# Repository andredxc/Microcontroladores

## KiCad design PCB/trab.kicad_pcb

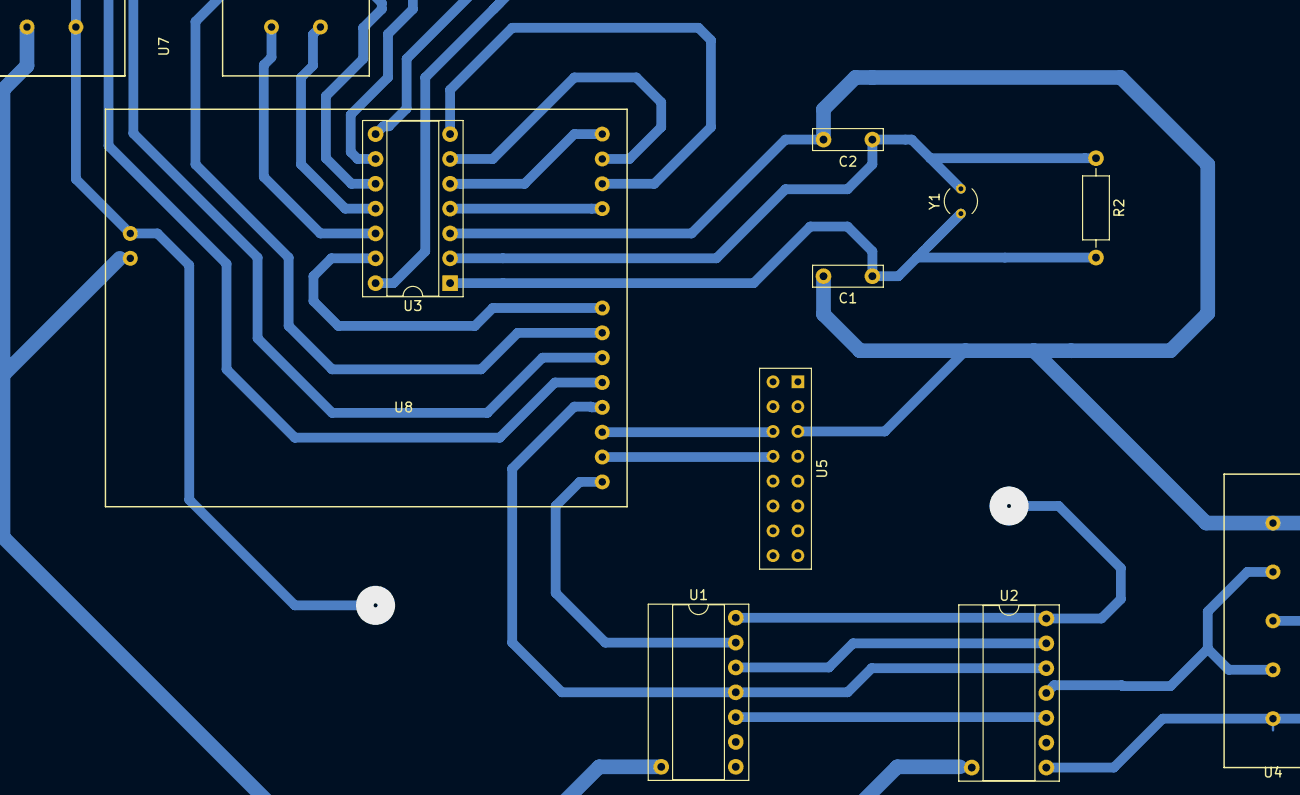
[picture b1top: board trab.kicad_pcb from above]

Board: 2 copper layers, 11 parts (0 on the bottom side), 22 nets.

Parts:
C1, C2: 22pF; C_Rect_L7.0mm_W2.0mm_P5.00mm
R2: 1M; R_Axial_DIN0207_L6.3mm_D2.5mm_P10.16mm_Horizontal
U1: 74LS04; DIP-14_W7.62mm_Socket
U2: 74LS08; DIP-14_W7.62mm_Socket
U3: LS7366R; DIP-14_W7.62mm_Socket
U4: L298N_2; krex5
U5: end; Samtec_HLE-116-02-xx-DV-TE_2x08_P2.54mm_Horizontal
U7: MotorEncoder; krex4
U8: GalileoGen2Shield; galileo
Y1: 30MHz; Crystal_AT310_D3.0mm_L10.0mm_Vertical

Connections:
/+5V: U1.14, U2.14, U3.14, U7.2, U8.28
/A_J1: U3.12, U7.3
/B_J1: U3.11, U7.4
/DFLAG_1: U3.9, U8.6
/ELB1: U5.6, U8.3
/ELB2: U5.8, U8.2
/ENABLE: U1.13, U8.1
/EN_1: U3.13, U8.8
/INDEX_1: U3.10, U8.7
/LFLAG_1: U3.8, U8.5
/MISO: U3.6, U8.13
/MOSI: U3.7, U8.12
/MOTOR: U1.11, U2.12, U8.4
/SCK: U3.5, U8.14
/SS: U3.4, U8.11
GND: C1.2, C2.2, U1.7, U2.7, U3.3, U4.6, U5.5, U7.1, U8.27
unnamed: C1.1, R2.2, U3.1, Y1.1
unnamed: C2.1, R2.1, U3.2, Y1.2
unnamed: U1.10, U2.10
unnamed: U1.12, U2.9, U2.13
unnamed: U2.8, U4.1, U4.3
unnamed: U2.11, U4.2, U4.4

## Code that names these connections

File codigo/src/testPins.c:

#include <stdio.h>
#include <stdlib.h>
#include <unistd.h>
#include <fcntl.h>
#include "libgalileo2.h"

// IO 00 gpio11 as input(LFLAG_1)
// IO 01 gpio12 as input (DFLAG_1)
// IO 02 gpio13 as output (INDEX_1)
// IO 03 pwm1 as output (MOTOR)
// IO 04 gpio6 as output(EN_1)
// IO 05 gpio0 as input (ELB1)
// IO 06 gpio1 as input (ELB2)
// IO 07 gpio38 as output (ENABLE)
// IO 10 gpio10 as output (SS)
// IO 11 (MOSI)
// IO 12 (MISO)
// IO 13 (SCK)

// Inputs
# define LFLAG "/sys/class/gpio/gpio11/value"
# define DFLAG "/sys/class/gpio/gpio12/value"
# define ELB1 "/sys/class/gpio/gpio0/value"
# define ELB2 "/sys/class/gpio/gpio1/value"
// Outputs
# define INDEX "/sys/class/gpio/gpio13/value"
# define EN "/sys/class/gpio/gpio6/value"
# define ENABLE "/sys/class/gpio/gpio38/value"

// PWM
#define PWM_DUTYCYCLE "/sys/class/pwm/pwmchip0/pwm1/duty_cycle"
#define PWM_ENABLE "/sys/class/pwm/pwmchip0/pwm1/enable"
#define PWM_PERIOD "/sys/class/pwm/pwmchip0/device/pwm_period"


int main(){

    int done, count;
    char buffer[30], outBuffer[10] = {"1"};

    pputs(PWM_PERIOD, "1000000");
    pputs(PWM_ENABLE, "1");

    done = 0;
    count = 0;
    while(!done){

        fprintf(stderr, ".\n");
        // Inputs ---------------------------------------------------------
        // LFLAG
        if(pgets(buffer, sizeof(buffer), LFLAG) < 0){
            fprintf(stderr, "Error reading %s\n", LFLAG);
        }
        if(atoi(buffer) == 1){
            fprintf(stderr, "LFLAG (IO 00) high\n");
        }
        // DFLAG
        if(pgets(buffer, sizeof(buffer), DFLAG) < 0){
            fprintf(stderr, "Error reading %s\n", DFLAG);
        }
        if(atoi(buffer) == 1){
            fprintf(stderr, "DFLAG (IO 01) high\n");
        }
        // ELB1
        if(pgets(buffer, sizeof(buffer), ELB1) < 0){
            fprintf(stderr, "Error reading %s\n", ELB1);
        }
        if(atoi(buffer) == 1){
            fprintf(stderr, "ELB1 (IO 05) high\n");
        }
        // ELB2
        if(pgets(buffer, sizeof(buffer), ELB2) < 0){
            fprintf(stderr, "Error reading %s\n", ELB2);
        }
        if(atoi(buffer) == 1){
            fprintf(stderr, "ELB2 (IO 06) high\n");
        }

        // Outputs ---------------------------------------------------------
        // INDEX
        if(pputs(INDEX, outBuffer) < 0){
            fprintf(stderr, "Error writing to %s\n", INDEX);
        }
        // ENABLE
        if(pputs(ENABLE, outBuffer) < 0){
            fprintf(stderr, "Error writing to %s\n", ENABLE);
        }
        // EN
        if(pputs(EN, outBuffer) < 0){
            fprintf(stderr, "Error writing to %s\n", EN);
        }

        // PWM ------------------------------------------------------------
        snprintf(buffer, sizeof(buffer), "%d\n", (int)(count/100.0 * 1000000.0));
        pputs(PWM_DUTYCYCLE, buffer);

        if(count >= 100){
            count = 0;
        }
        else{
            count += 5;
        }

        if(outBuffer[0] == '1'){
            outBuffer[0] = '0';
        }
        else{
            outBuffer[0] = '1';
        }

        usleep(500000);
    }

    return 1;

    /*
    int elb1_fd, elb2_fd;
    char elb1_buffer[10], elb2_buffer[10];

    // Elbow sensors
    elb1_fd = open(ELB1_VALUE, O_RDONLY);
    if(elb1_fd < 0){
        fprintf(stderr, "Error opening %s\n", ELB1_VALUE);
        close(elb1_fd);
        close(elb2_fd);
        return -1;
    }
    elb2_fd = open(ELB2_VALUE, O_RDONLY);
    if(elb2_fd < 0){
        fprintf(stderr, "Error opening %s\n", ELB2_VALUE);
        close(elb1_fd);
        close(elb2_fd);
        return -1;
    }

    // Read initial values from elbow sensors
    if(read(elb1_fd, elb1_buffer, sizeof(elb1_buffer)) < 0){
        fprintf(stderr, "Error reading from elb1_fd\n");
        close(elb1_fd);
        close(elb2_fd);
        return -1;
    }
    if(read(elb2_fd, elb2_buffer, sizeof(elb2_buffer))){
        fprintf(stderr, "Error reading from elb2_fd\n");
        close(elb1_fd);
        close(elb2_fd);
        return -1;
    }

    while(atoi(elb1_buffer) == 0 && atoi(elb2_buffer) == 0){
        // Arm has not reached end of course





        if(read(elb1_fd, elb1_buffer, sizeof(elb1_buffer)) < 0){
            fprintf(stderr, "Error reading from elb1_fd\n");
            close(elb1_fd);
            close(elb2_fd);
            return -1;
        }
        if(read(elb2_fd, elb2_buffer, sizeof(elb2_buffer))){
            fprintf(stderr, "Error reading from elb2_fd\n");
            close(elb1_fd);
            close(elb2_fd);
            return -1;
        }
        usleep(1000);
    }





    close(elb1_fd);
    close(elb2_fd);
    return 0;
    */
}

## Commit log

2018-10-06 Começando
2018-10-07 Continuando esquemático
2018-10-07 Arrumando pastas
2018-10-11 Terminando esquemático
2018-10-11 Versão entregue
2018-11-27 Começando script
2018-11-27 Terminando init
2018-11-29 Codigo
2018-12-01 Terminando e testando script de inicialização
2018-12-01 Removendo programas inúteis
2018-12-04 Começando api
2018-12-11 Adicionando funções a API
2018-12-11 Layout
2018-12-11 PCB versao 2
2018-12-12 Atualizando pinos
2018-12-12 Terminando layout e entrega
2018-12-12 Entraga
2018-12-12 Atualizando fim de curso
2018-12-12 testEncoer
2018-12-12 Final 2
